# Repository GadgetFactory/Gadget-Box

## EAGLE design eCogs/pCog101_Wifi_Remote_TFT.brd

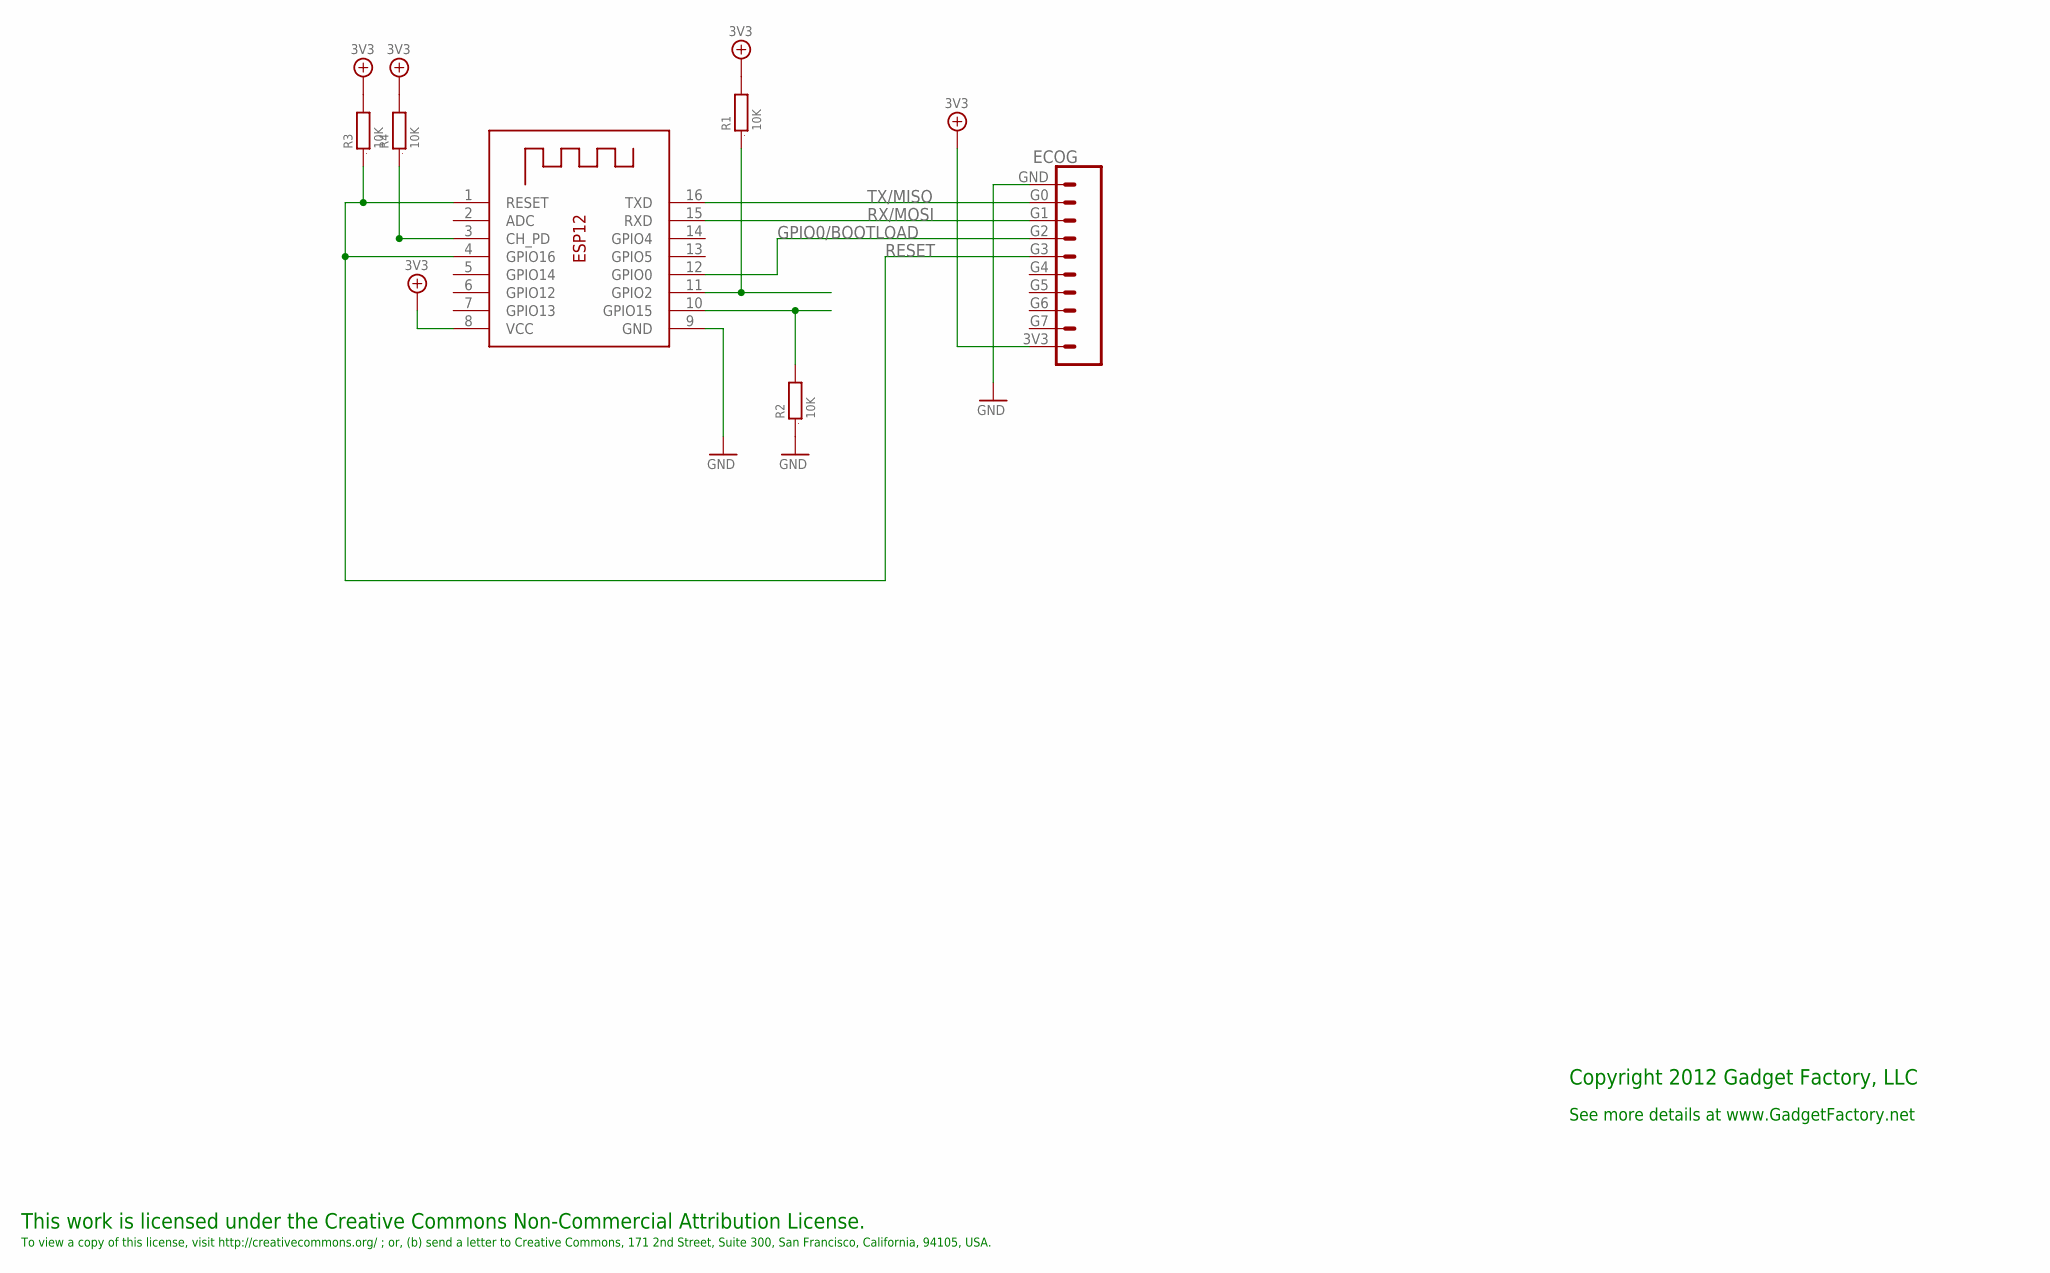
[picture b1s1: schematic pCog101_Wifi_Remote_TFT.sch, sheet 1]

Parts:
ECOG: ECOG_GENERAL_ROWTHROUGHOLE; ECOG_GENERAL_TH
R1, R2, R3, R4: 10K; 0805; DIGIKEY RMCF0805JT10K0CT-ND
X1: ESP-12

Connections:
3V3: ECOG.3V3, R1.2, R3.2, R4.2, X1.8 (VCC); also elsewhere on the board
GND: ECOG.GND, R2.1, X1.9 (GND); also elsewhere on the board
GPIO0/BOOTLOAD: ECOG.G2, X1.12 (GPIO0)
unnamed: R1.1, X1.11 (GPIO2)
unnamed: R2.2, X1.10 (GPIO15)
unnamed: R4.1, X1.3 (CH_PD)
RESET: ECOG.G3, R3.1, X1.1 (RESET), X1.4 (GPIO16)
RX/MOSI: ECOG.G1, X1.15 (RXD)
TX/MISO: ECOG.G0, X1.16 (TXD)

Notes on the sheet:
This work is licensed under the Creative Commons Non-Commercial Attribution License.
To view a copy of this license, visit http://creativecommons.org/ ; or, (b) send a letter to Creative Commons, 171 2nd Street, Suite 300, San Francisco, California, 94105, USA.
Copyright 2012 Gadget Factory, LLC
See more details at www.GadgetFactory.net

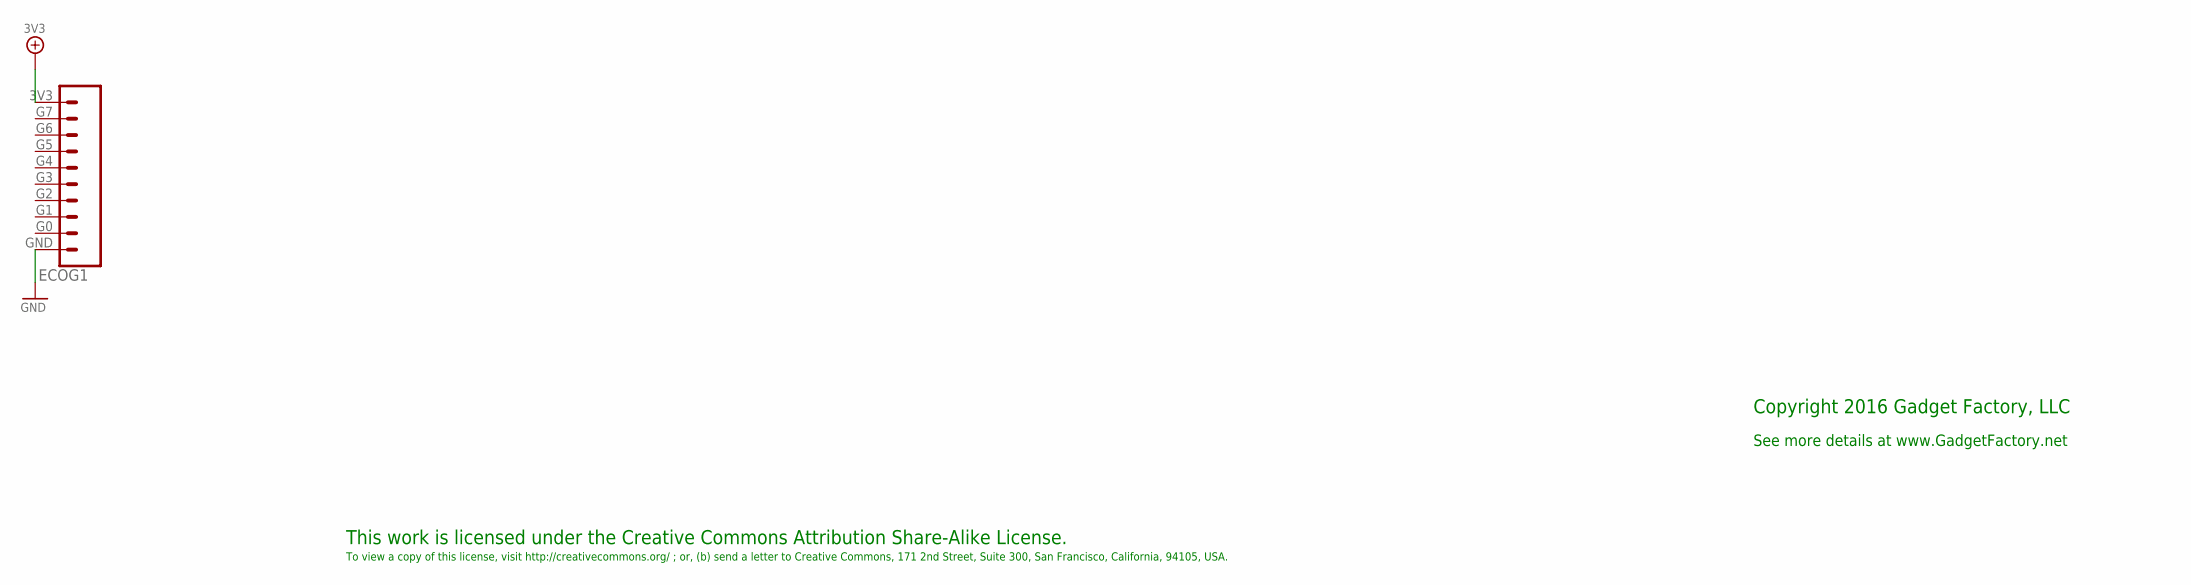
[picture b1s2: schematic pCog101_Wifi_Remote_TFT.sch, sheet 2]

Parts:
ECOG1: ECOG_GENERAL_ROWSURFACEMOUNT; ECOG_GENERAL_SMD

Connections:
3V3: ECOG1.3V3; also elsewhere on the board
GND: ECOG1.GND; also elsewhere on the board

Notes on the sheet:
This work is licensed under the Creative Commons Attribution Share-Alike License.
To view a copy of this license, visit http://creativecommons.org/ ; or, (b) send a letter to Creative Commons, 171 2nd Street, Suite 300, San Francisco, California, 94105, USA.
Copyright 2016 Gadget Factory, LLC
See more details at www.GadgetFactory.net

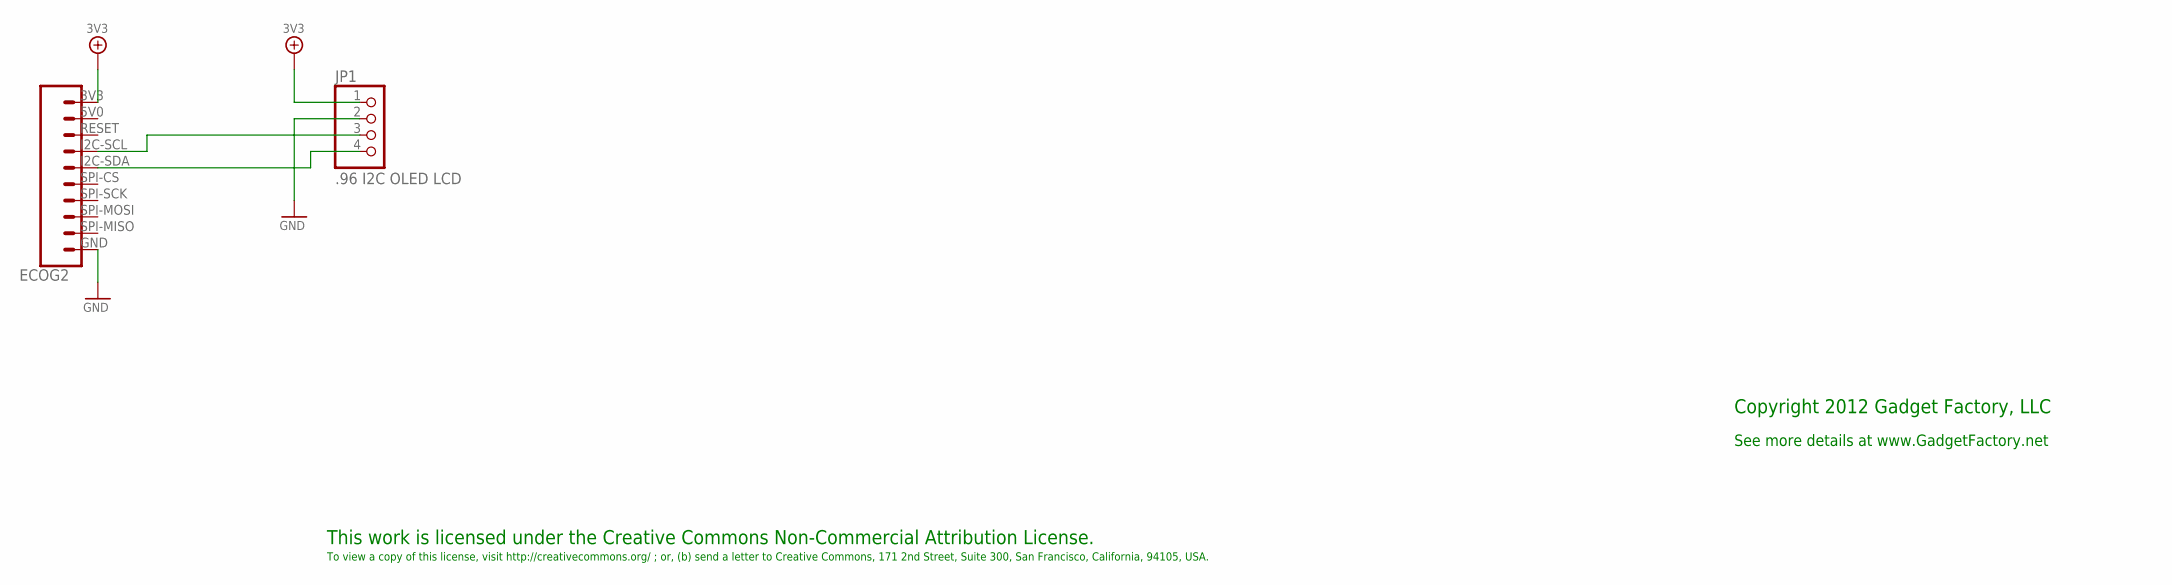
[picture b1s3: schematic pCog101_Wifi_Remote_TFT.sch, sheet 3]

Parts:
ECOG2: ECOG_BUSES_ROWTHROUGHHOLE; ECOG_BUSES_TH
JP1: .96 I2C OLED LCD; 1X04

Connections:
3V3: ECOG2.3V3, JP1.1; also elsewhere on the board
GND: ECOG2.GND, JP1.2; also elsewhere on the board
unnamed: ECOG2.I2C-SCL, JP1.3
unnamed: ECOG2.I2C-SDA, JP1.4

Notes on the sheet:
This work is licensed under the Creative Commons Non-Commercial Attribution License.
To view a copy of this license, visit http://creativecommons.org/ ; or, (b) send a letter to Creative Commons, 171 2nd Street, Suite 300, San Francisco, California, 94105, USA.
Copyright 2012 Gadget Factory, LLC
See more details at www.GadgetFactory.net

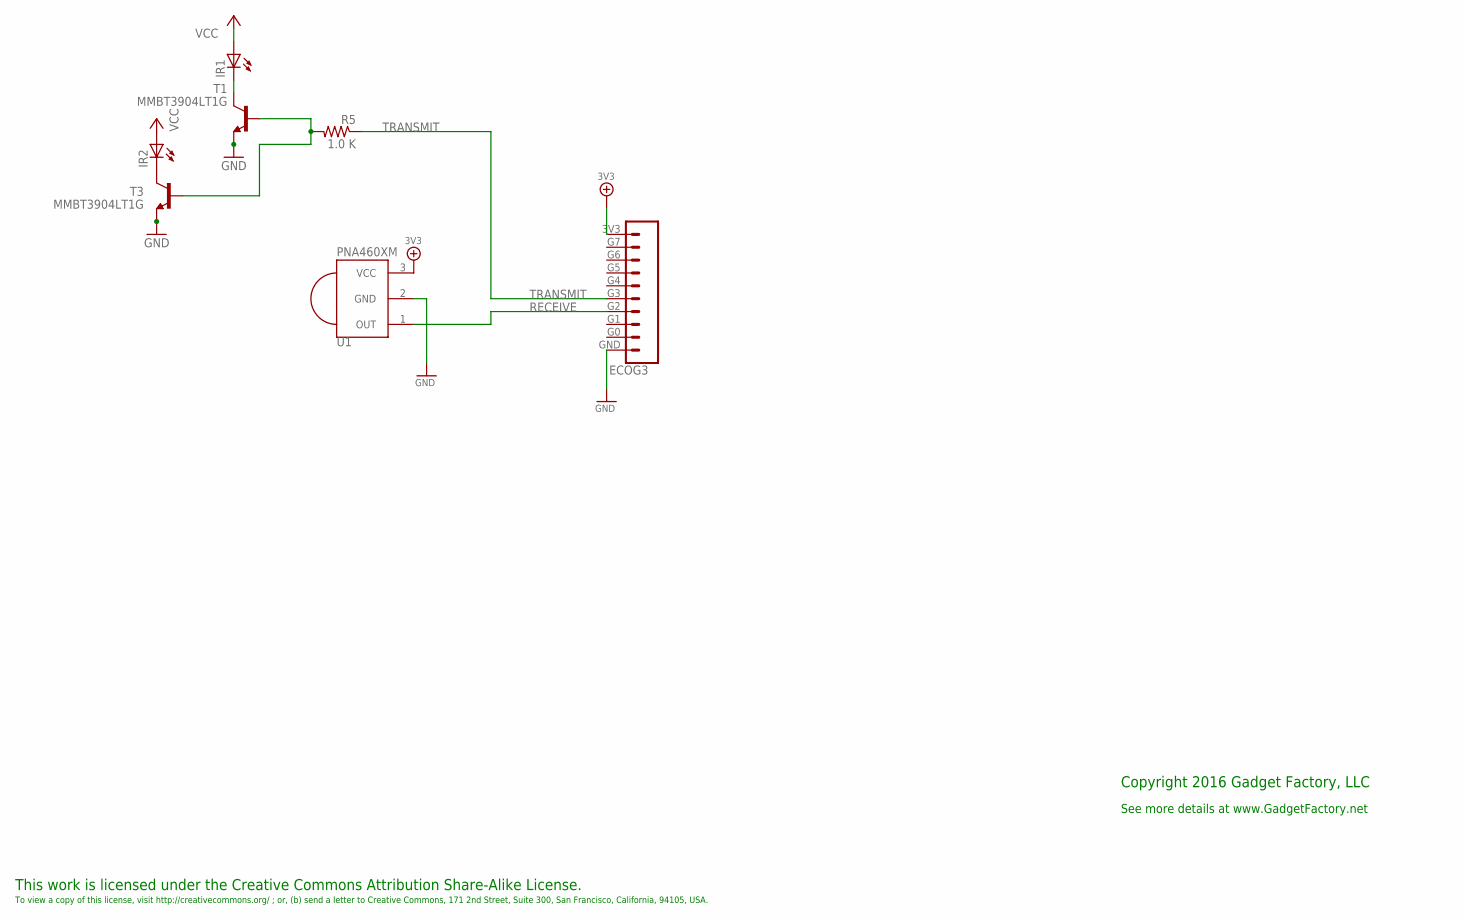
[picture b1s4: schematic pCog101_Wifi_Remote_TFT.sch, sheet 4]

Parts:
ECOG3: ECOG_GENERAL_ROWTHROUGHOLE; ECOG_GENERAL_TH
IR1: LED5MM; DIGIKEY 1080-1082-ND
IR2: LED5MM; DIGIKEY 1080-1080-ND
R5: 1.0 K; R0805; DIGIKEY 311-1.0KARCT-ND
T1, T3: MMBT3904LT1G; SOT23-BEC; DIGIKEY MMBT3904LT1GOSCT-ND
U1: PNA460XM; DIGIKEY 751-1227-ND

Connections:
3V3: ECOG3.3V3, IR1.A, IR2.A, U1.3 (VCC); also elsewhere on the board
GND: ECOG3.GND, T1.E, T3.E, U1.2 (GND); also elsewhere on the board
unnamed: IR1.K (C), T1.C
unnamed: IR2.K (C), T3.C
unnamed: R5.2, T1.B, T3.B
RECEIVE: ECOG3.G2, U1.1 (OUT)
TRANSMIT: ECOG3.G3, R5.1

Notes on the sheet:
This work is licensed under the Creative Commons Attribution Share-Alike License.
To view a copy of this license, visit http://creativecommons.org/ ; or, (b) send a letter to Creative Commons, 171 2nd Street, Suite 300, San Francisco, California, 94105, USA.
Copyright 2016 Gadget Factory, LLC
See more details at www.GadgetFactory.net

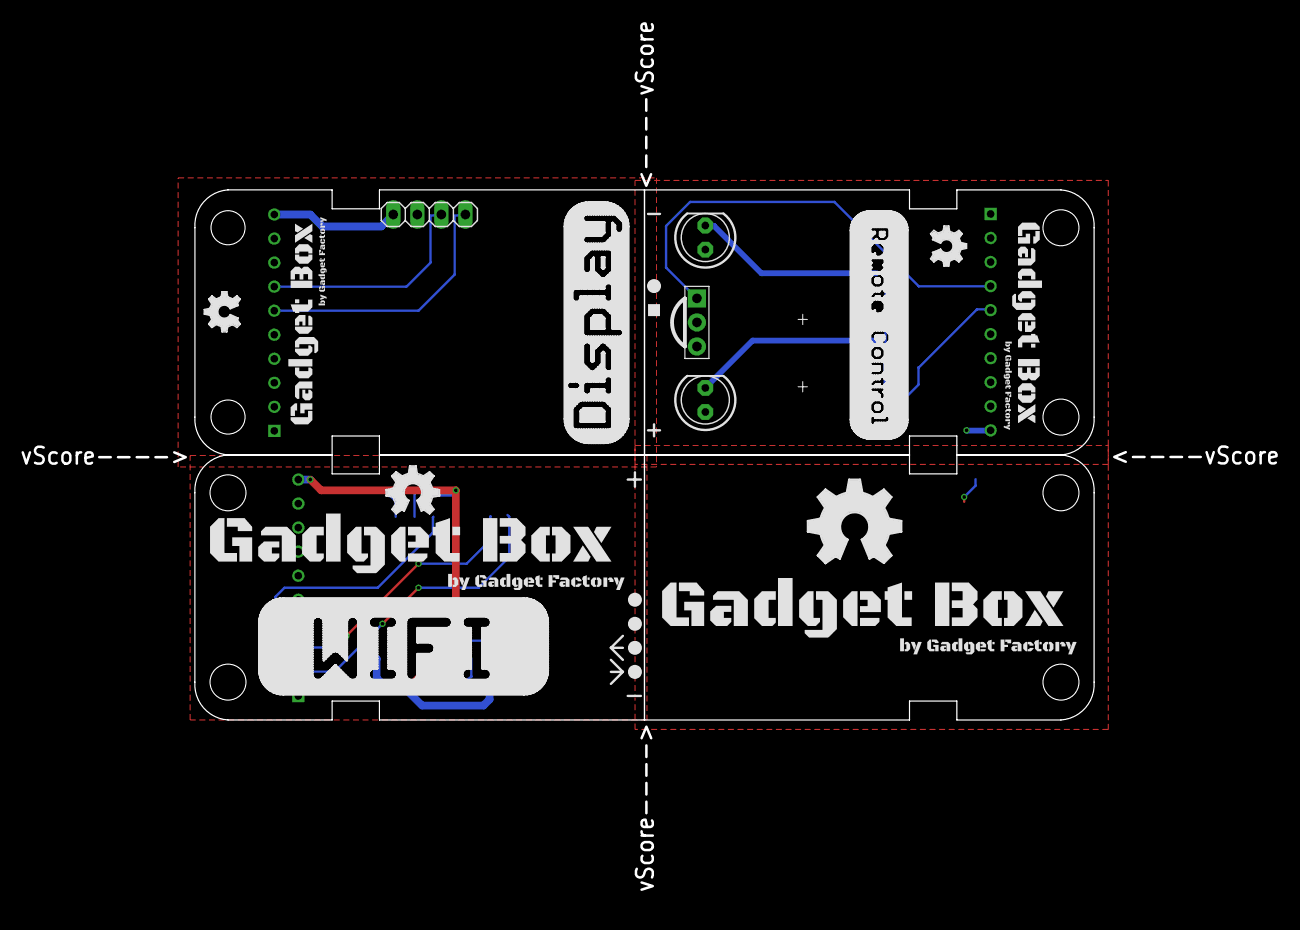
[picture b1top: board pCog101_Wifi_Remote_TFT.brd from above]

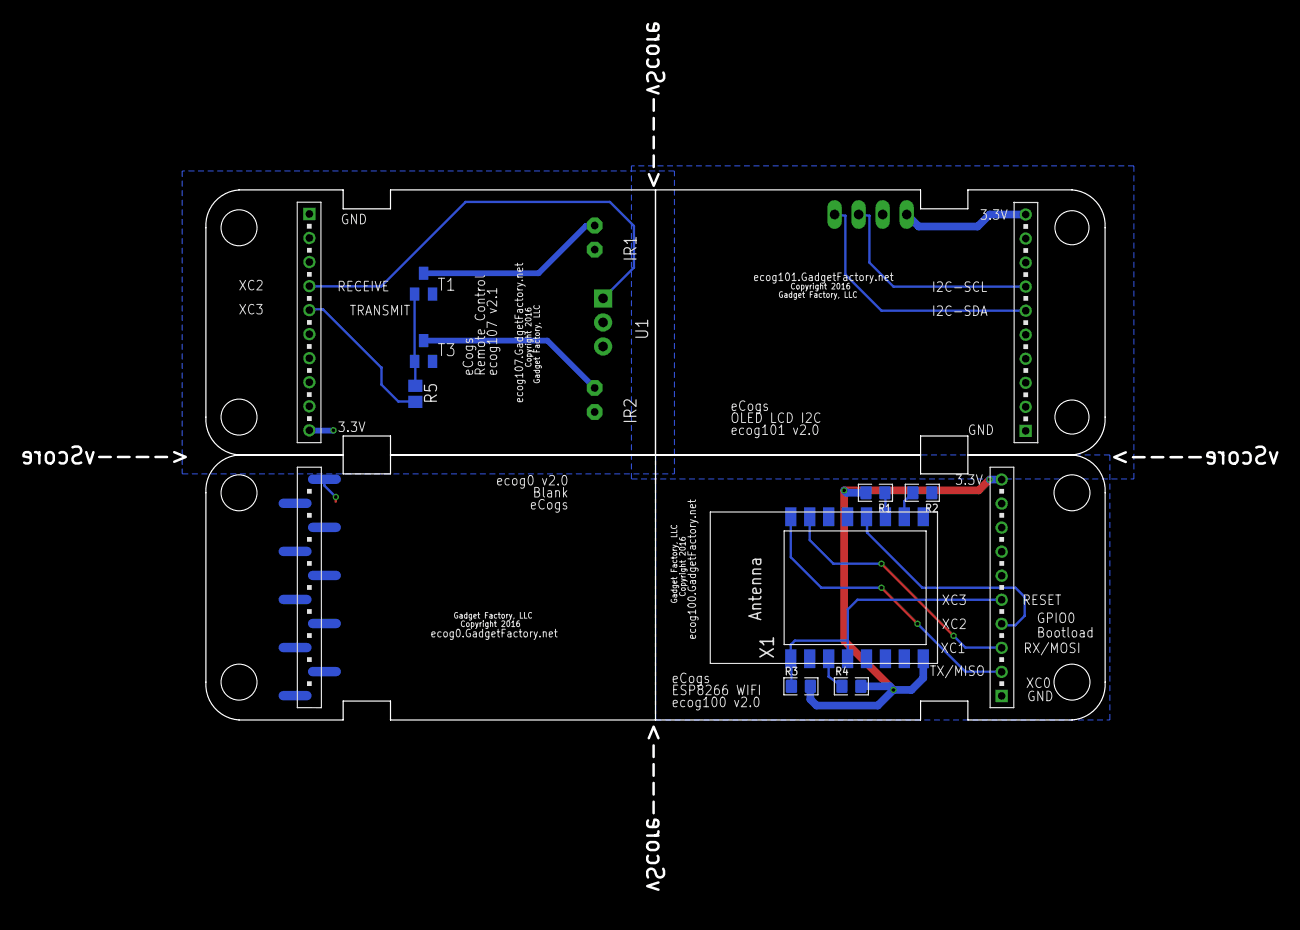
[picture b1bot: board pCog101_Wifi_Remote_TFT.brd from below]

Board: 2 copper layers, 95.0 x 56.0 mm, 30 parts (8 on the bottom side), 16 nets.

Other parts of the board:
U$1, U$7: GADGETBOX_TEXT
U$2, U$3, U$4, U$5, U$14: LEGEND_DIO
U$6: OSHW_FILLX200_NOTEXT
U$8: OSHW_FILLX350_NOTEXT
U$9, U$11: GADGETBOX_SMALL
U$10, U$12: OSHW_FILLX150_NOTEXT
U$13: LEGEND_PWM

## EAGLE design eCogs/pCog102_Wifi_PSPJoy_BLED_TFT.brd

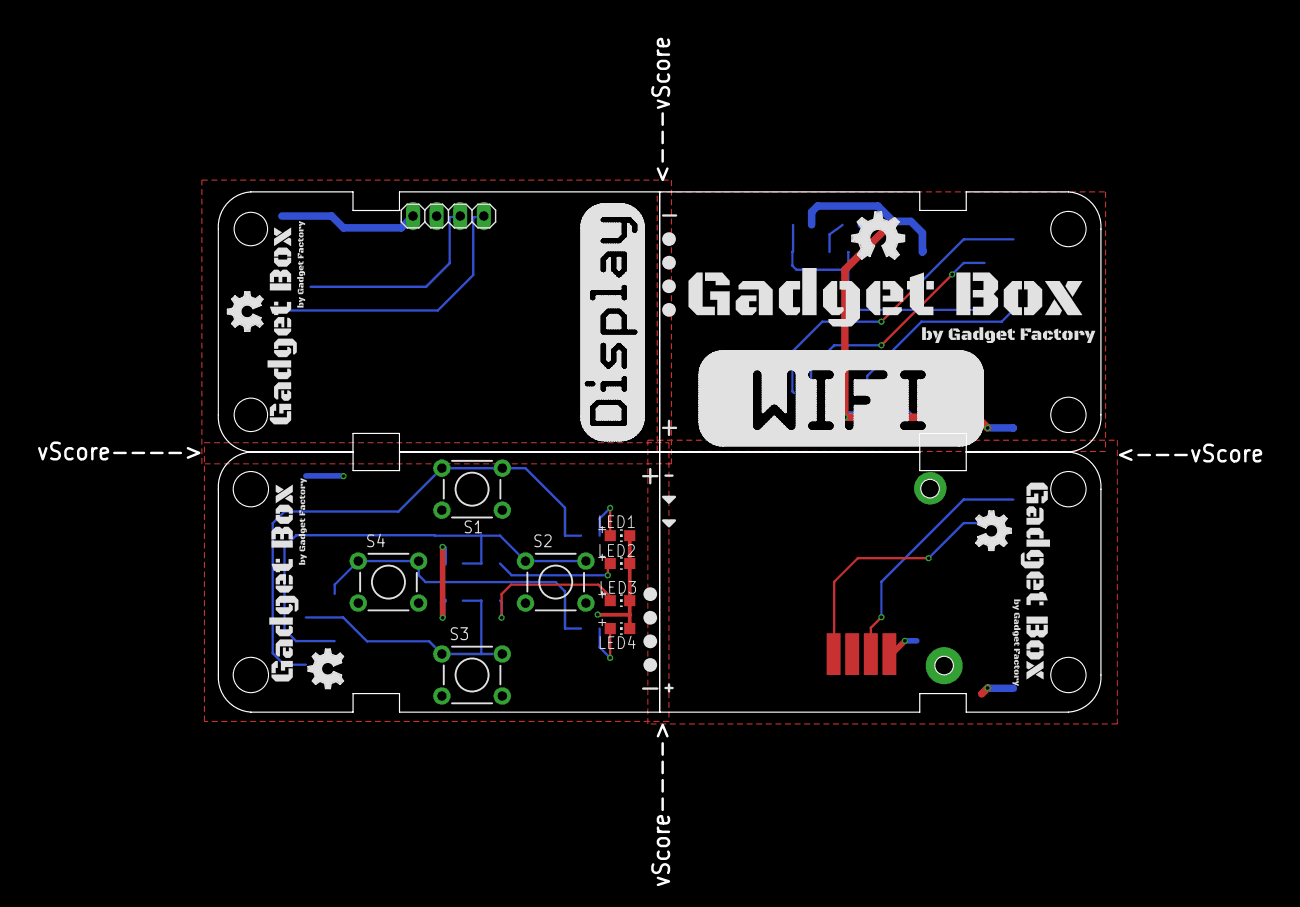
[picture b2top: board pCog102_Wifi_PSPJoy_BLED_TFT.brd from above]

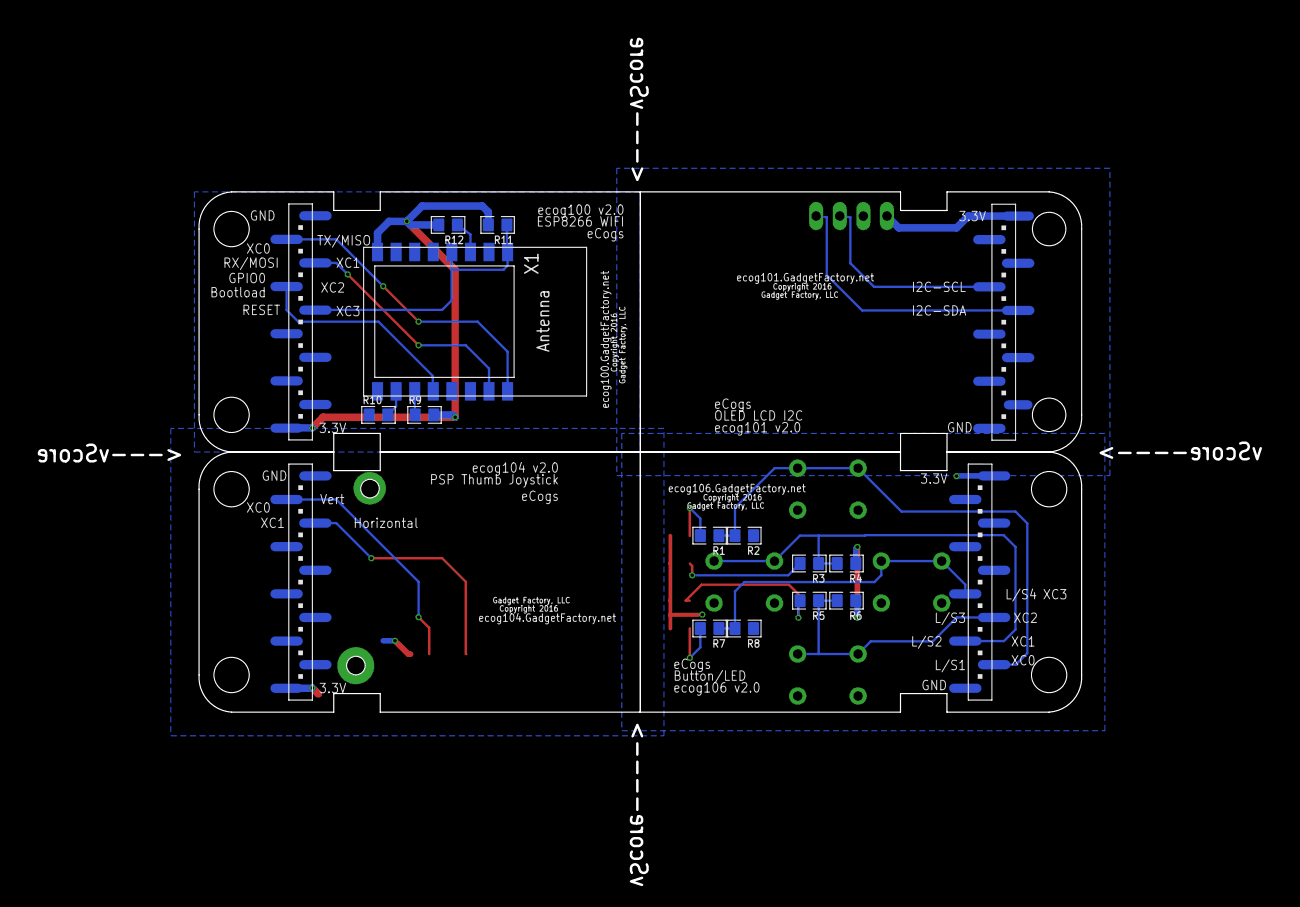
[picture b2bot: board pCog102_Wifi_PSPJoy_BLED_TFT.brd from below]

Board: 2 copper layers, 95.0 x 56.0 mm, 45 parts (13 on the bottom side), 21 nets.

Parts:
ECOG, ECOG1, ECOG3: ECOG_GENERAL_ROWECOG_GENERAL_SMD; ECOG_GENERAL_SMD
ECOG2: ECOG_BUSES_ROWECOG_BUSES_SMD; ECOG_BUSES_SMD
JP1: .96 I2C OLED LCD; 1X04
LED1, LED2, LED3, LED4: CHIP-LED0805
R1, R3, R5, R7: 390; 0805
R2, R4, R6, R8, R9, R10, R11, R12: 10K; 0805
S1, S2, S3, S4: TACTILE-PTH
U$1, U$2, U$3, U$4, U$15, U$16, U$17, U$18: LEGEND_DIO
U$5, U$10, U$12: GADGETBOX_SMALL
U$6, U$11, U$13: OSHW_FILLX150_NOTEXT
U$7: JOYSTICK-PSP1000
U$8, U$9: LEGEND_ANALOG
U$14: GADGETBOX_TEXT
U$19: OSHW_FILLX200_NOTEXT
X1: ESP-12

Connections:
1: ECOG.G0, R1.1, R2.2, S1.1, S1.2
2: ECOG.G1, R3.1, R4.2, S2.1, S2.2
3: ECOG.G2, R5.1, R6.2, S3.1, S3.2
3V3: ECOG.3V3, ECOG1.3V3, ECOG2.3V3, ECOG3.3V3, JP1.1, R9.2, R11.2, R12.2, S1.3, S1.4, S2.3, S2.4, S3.3, S3.4, S4.3, S4.4, U$7.VCC, X1.8
4: ECOG.G3, R7.1, R8.2, S4.1, S4.2
GND: ECOG.GND, ECOG1.GND, ECOG2.GND, ECOG3.GND, JP1.2, LED1.C, LED2.C, LED3.C, LED4.C, R2.1, R4.1, R6.1, R8.1, R10.1, U$7.GND, X1.9
GPIO0/BOOTLOAD: ECOG3.G2, X1.12
HORIZONTAL: ECOG1.G1, U$7.X
unnamed: LED1.A, R1.2
unnamed: LED2.A, R3.2
unnamed: LED3.A, R5.2
unnamed: LED4.A, R7.2
unnamed: ECOG2.I2C-SDA, JP1.4
unnamed: ECOG2.I2C-SCL, JP1.3
unnamed: R9.1, X1.11
unnamed: R10.2, X1.10
unnamed: R12.1, X1.3
RESET: ECOG3.G3, R11.1, X1.1, X1.4
RX/MOSI: ECOG3.G1, X1.15
TX/MISO: ECOG3.G0, X1.16
VERTICAL: ECOG1.G0, U$7.Y

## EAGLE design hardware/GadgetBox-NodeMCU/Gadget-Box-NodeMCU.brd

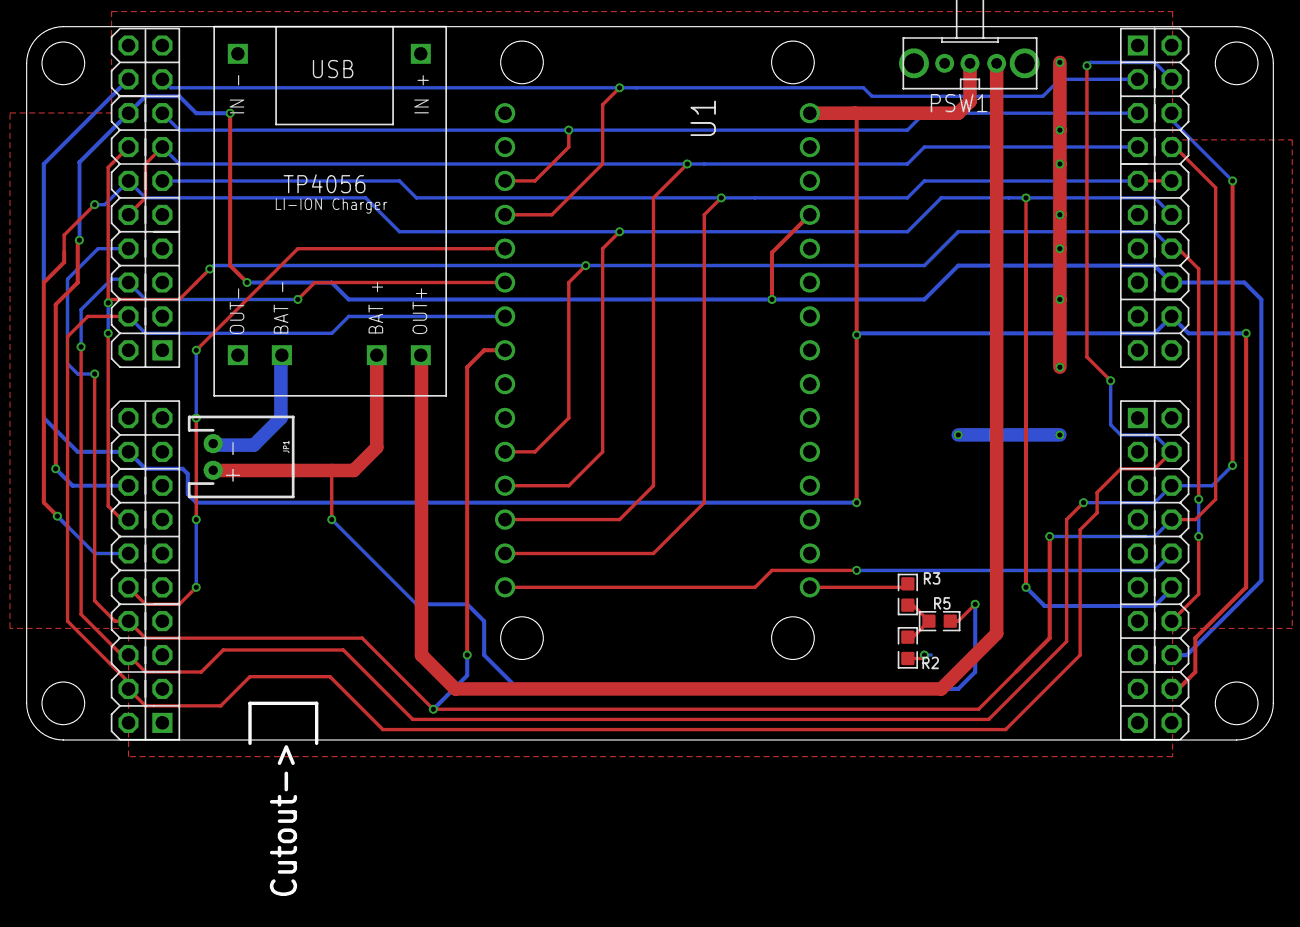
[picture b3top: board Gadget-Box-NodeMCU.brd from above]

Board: 2 copper layers, 93.5 x 53.5 mm, 13 parts (1 on the bottom side), 19 nets.

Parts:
$$U$1: ECOG93P53P5
AH: ECOGECOG_SLOT; ECOG
AL: ECOGECOG_SLOT; ECOG
BH: ECOGECOG_SLOT; ECOG
BL: ECOGECOG_SLOT; ECOG
JP1: JST-2-PTH-NS
PSW1: OS102011MA1Q
R2, R5: 100k; 0603
R3: DNP; 0603
U1: ESP12E_DEVKIT
U$1: TP4056
U$100: GADGETBOX_TEXT

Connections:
3V3: AH.3V3@B8, AH.3V3@G8, AL.3V3@B8, AL.3V3@G8, BH.3V3@B8, BH.3V3@G8, BL.3V3@B8, BL.3V3@G8, U1.3V3@0, U1.3V3@1, U1.3V3@2
ADC: R3.1, U1.AD0
D0/RX/MISO: AL.G0, BH.G7, U1.RX
D1/TX/MOSI: AL.G1, BH.G6, U1.TX
D2: AL.G2, BH.G5, BH.SPI-CS@B3, U1.D2
D3: AL.G3, AL.SPI-CS@B3, BH.G4, U1.D1
GND: AH.GND@B, AH.GND@G, AL.GND@B, AL.GND@G, BH.GND@B, BH.GND@G, BL.GND@B, BL.GND@G, JP1.1, R2.1, U1.GND@0, U1.GND@1, U1.GND@2, U1.GND@3, U$1.BAT-, U$1.IN-, U$1.OUT-
I2C-SCL: AH.I2C-SCL@B5, AL.I2C-SCL@B5, BH.I2C-SCL@B5, BL.I2C-SCL@B5, U1.D4
I2C-SDA/BOOTLOAD: AH.I2C-SDA@B4, AL.I2C-SDA@B4, BH.I2C-SDA@B4, BL.I2C-SDA@B4, U1.D3
unnamed: R2.2, R3.2, R5.1
unnamed: PSW1.1, U$1.OUT+
RESET: AH.RESET@B6, AL.RESET@B6, BH.RESET@B6, BL.RESET@B6, U1.EN
SPI-CSC: BL.SPI-CS@B3, U1.D8
SPI-CSD: AH.SPI-CS@B3, U1.D0
SPI-MISO: AH.SPI-MISO@B0, AL.SPI-MISO@B0, BH.SPI-MISO@B0, BL.SPI-MISO@B0, U1.D6
SPI-MOSI: AH.SPI-MOSI@B1, AL.SPI-MOSI@B1, BH.SPI-MOSI@B1, BL.SPI-MOSI@B1, U1.D7
SPI-SCK: AH.SPI-SCK@B2, AL.SPI-SCK@B2, BH.SPI-SCK@B2, BL.SPI-SCK@B2, U1.D5
VBAT: JP1.2, R5.2, U$1.BAT+
VIN: AH.5V@B7, AL.5V@B7, BH.5V@B7, BL.5V@B7, PSW1.2, U1.VIN

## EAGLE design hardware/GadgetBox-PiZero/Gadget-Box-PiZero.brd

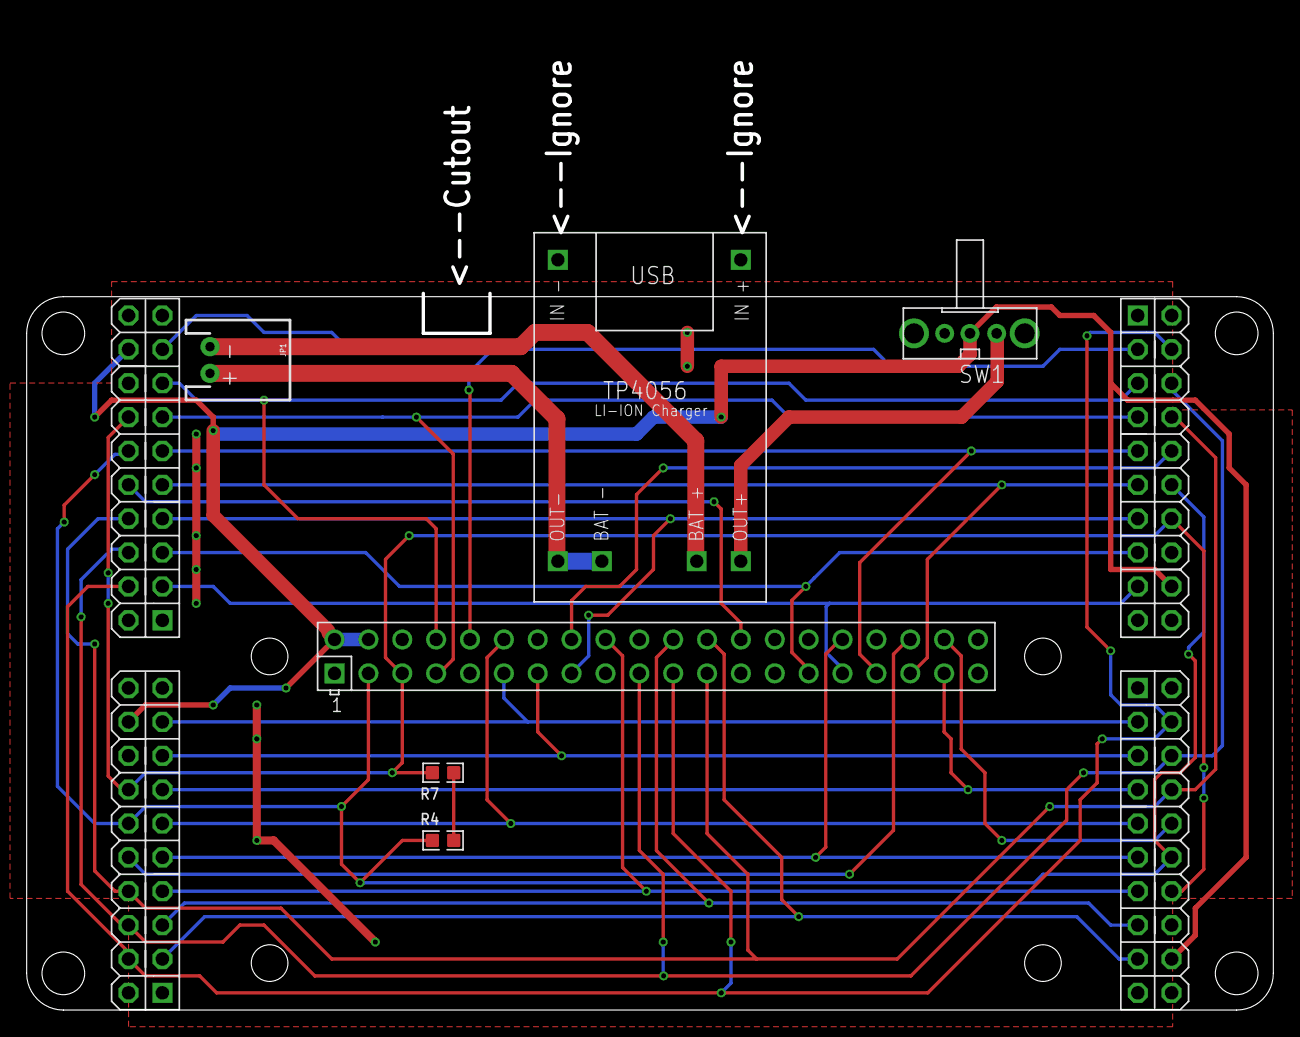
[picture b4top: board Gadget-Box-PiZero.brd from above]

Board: 2 copper layers, 93.5 x 53.5 mm, 12 parts (1 on the bottom side), 30 nets.

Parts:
$$U$1: ECOG93P53P5
AH: ECOGECOG_SLOT_ALT1; ECOG_ALT1
AL: ECOGECOG_SLOT_ALT1; ECOG_ALT1
BH: ECOGECOG_SLOT_ALT1; ECOG_ALT1
BL: ECOGECOG_SLOT_ALT1; ECOG_ALT1
JP1: JST-2-PTH-NS
R4, R7: 10K; 0603
SW1: OS102011MA1Q
U$1: RPI-ZERO; RASPBERRYPI_BASTELSTUBE_V13_RASPI_BOARD_B+_FULL
U$2: TP4056
U$100: GADGETBOX_TEXT

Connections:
3V3: AH.3V3@B8, AH.3V3@G8, AL.3V3@B8, AL.3V3@G8, BH.3V3@B8, BH.3V3@G8, BL.3V3@B8, BL.3V3@G8, R4.2, R7.2, U$1.1, U$1.17
5V0: AH.5V@B7, AL.5V@B7, BH.5V@B7, BL.5V@B7, SW1.2, U$1.2, U$1.4
D0/RX/MISO: AL.G0, BH.G7, U$1.10
D1/TX/MOSI: AL.G1, BH.G6, U$1.8
D2: AL.G2, BH.G5, U$1.7
D3*: AL.G3, BH.G4, U$1.33
D4*: AL.G4, BH.G3, U$1.35
D5: AL.G5, BH.G2, U$1.15
D6: AL.G6, BH.G1, U$1.29
D7: AL.G7, BH.G0, U$1.31
D8: AH.G0, BL.G7, U$1.11
D9: AH.G1, BL.G6, U$1.13
D10: AH.G2, BL.G5, U$1.37
D11*: AH.G3, BL.G4, U$1.12
D12*: AH.G4, BL.G3, U$1.32
D13: AH.G5, BL.G2, U$1.18
D14: AH.G6, BL.G1, U$1.22
D15: AH.G7, BL.G0, U$1.24
GND: AH.GND@B, AH.GND@G, AL.GND@B, AL.GND@G, BH.GND@B, BH.GND@G, BL.GND@B, BL.GND@G, JP1.2, U$1.6, U$1.9, U$1.14, U$1.20, U$1.25, U$1.30, U$1.34, U$1.39, U$2.BAT-, U$2.OUT-
I2C-SCL: AH.I2C-SCL@B5, AL.I2C-SCL@B5, BH.I2C-SCL@B5, BL.I2C-SCL@B5, R7.1, U$1.5
I2C-SDA: AH.I2C-SDA@B4, AL.I2C-SDA@B4, BH.I2C-SDA@B4, BL.I2C-SDA@B4, R4.1, U$1.3
unnamed: JP1.1, U$2.BAT+
unnamed: SW1.1, U$2.OUT+
SPI-CSA: BH.SPI-CS@B3, U$1.26
SPI-CSB: AL.SPI-CS@B3, U$1.16
SPI-CSC: BL.SPI-CS@B3, U$1.36
SPI-CSD: AH.SPI-CS@B3, U$1.38
SPI-MISO: AH.SPI-MISO@B0, AL.SPI-MISO@B0, BH.SPI-MISO@B0, BL.SPI-MISO@B0, U$1.21
SPI-MOSI: AH.SPI-MOSI@B1, AL.SPI-MOSI@B1, BH.SPI-MOSI@B1, BL.SPI-MOSI@B1, U$1.19
SPI-SCK: AH.SPI-SCK@B2, AL.SPI-SCK@B2, BH.SPI-SCK@B2, BL.SPI-SCK@B2, U$1.23

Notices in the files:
parts and their libraries:
SparkFun: Licensing: CC v3.0 Share-Alike You are welcome to use this library for commercial purposes.
